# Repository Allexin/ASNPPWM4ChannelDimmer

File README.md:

# ASNPPWM4ChannelDimmer
ASNP pwm dimmer with 4 AC 220v channels

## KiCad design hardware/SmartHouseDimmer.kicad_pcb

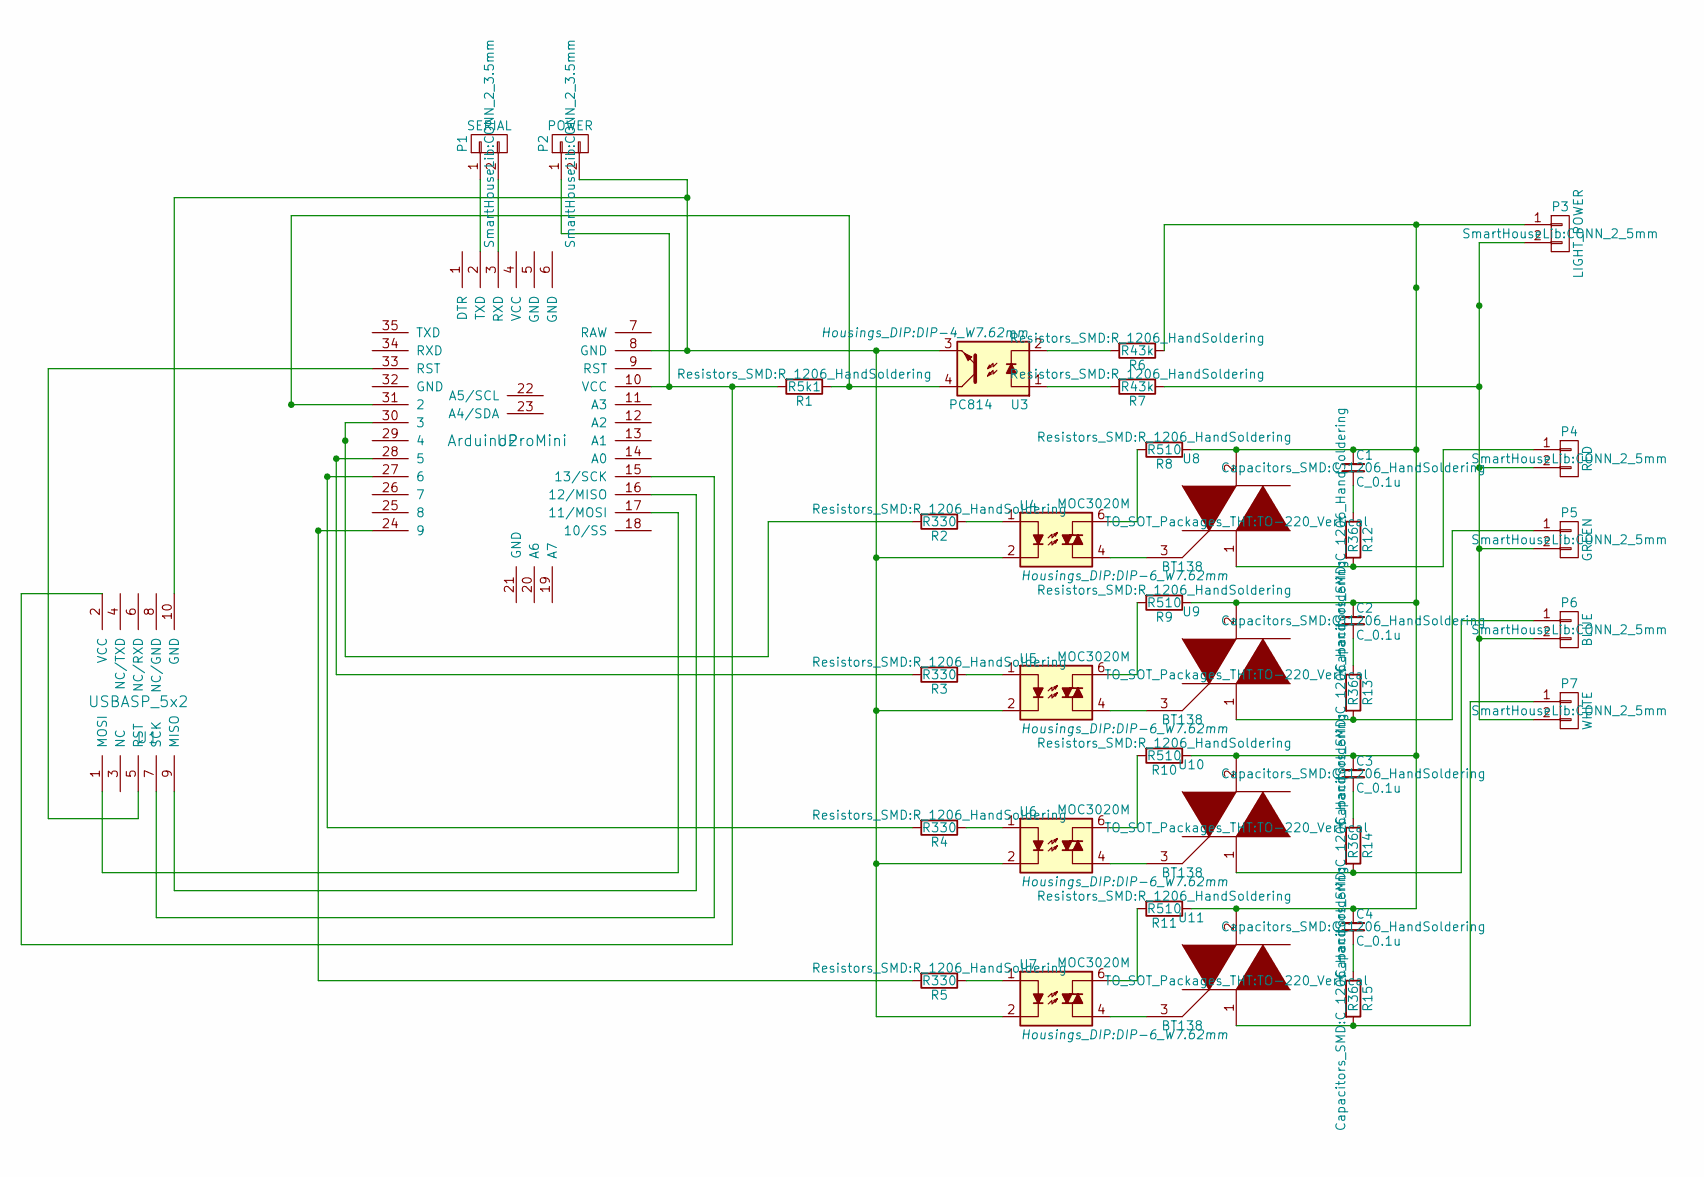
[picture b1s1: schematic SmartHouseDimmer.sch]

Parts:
C1, C2, C3, C4: C_0.1u; C_1206_HandSoldering
P1: SERIAL; CONN_2_3.5mm
P2: POWER; CONN_2_3.5mm
P3: LIGHT_POWER; CONN_2_5mm
P4: RED; CONN_2_5mm
P5: GREEN; CONN_2_5mm
P6: BLUE; CONN_2_5mm
P7: WHITE; CONN_2_5mm
R1: R5k1; R_1206_HandSoldering
R2, R3, R4, R5: R330; R_1206_HandSoldering
R6, R7: R43k; R_1206_HandSoldering
R8, R9, R10, R11: R510; R_1206_HandSoldering
R12, R13, R14, R15: R36; C_1206_HandSoldering
U1: USBASP_5x2; Pin_Header_Straight_2x05_Pitch2.54mm
U2: ArduinoProMini
U3: PC814; DIP-4_W7.62mm
U4, U5, U6, U7: MOC3020M; DIP-6_W7.62mm
U8, U9, U10, U11: BT138; TO-220_Vertical

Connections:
unnamed: C1.1, C2.1, C3.1, C4.1, P3.1, R6.1, R8.1, R9.1, R10.1, R11.1, U8.2, U9.2, U10.2, U11.2
unnamed: C1.2, R12.1
unnamed: C2.2, R13.1
unnamed: C3.2, R14.1
unnamed: C4.2, R15.1
unnamed: P1.1, U2.2 (TXD)
unnamed: P1.2, U2.3 (RXD)
unnamed: P2.1, R1.2, U1.2 (VCC), U2.10 (VCC)
unnamed: P2.2, U1.10 (GND), U2.8 (GND), U3.3, U4.2, U5.2, U6.2, U7.2
unnamed: P3.2, P4.2, P5.2, P6.2, P7.2, R7.1
unnamed: P4.1, R12.2, U8.1
unnamed: P5.1, R13.2, U9.1
unnamed: P6.1, R14.2, U10.1
unnamed: P7.1, R15.2, U11.1
unnamed: R1.1, U2.31 (2), U3.4
unnamed: R2.1, U4.1
unnamed: R2.2, U2.30 (3)
unnamed: R3.1, U5.1
unnamed: R3.2, U2.28 (5)
unnamed: R4.1, U6.1
unnamed: R4.2, U2.27 (6)
unnamed: R5.1, U7.1
unnamed: R5.2, U2.24 (9)
unnamed: R6.2, U3.2
unnamed: R7.2, U3.1
unnamed: R8.2, U4.6
unnamed: R9.2, U5.6
unnamed: R10.2, U6.6
unnamed: R11.2, U7.6
unnamed: U1.1 (MOSI), U2.17 (11/MOSI)
unnamed: U1.5 (RST), U2.33 (RST)
unnamed: U1.7 (SCK), U2.15 (13/SCK)
unnamed: U1.9 (MISO), U2.16 (12/MISO)
unnamed: U4.4, U8.3
unnamed: U5.4, U9.3
unnamed: U6.4, U10.3
unnamed: U7.4, U11.3

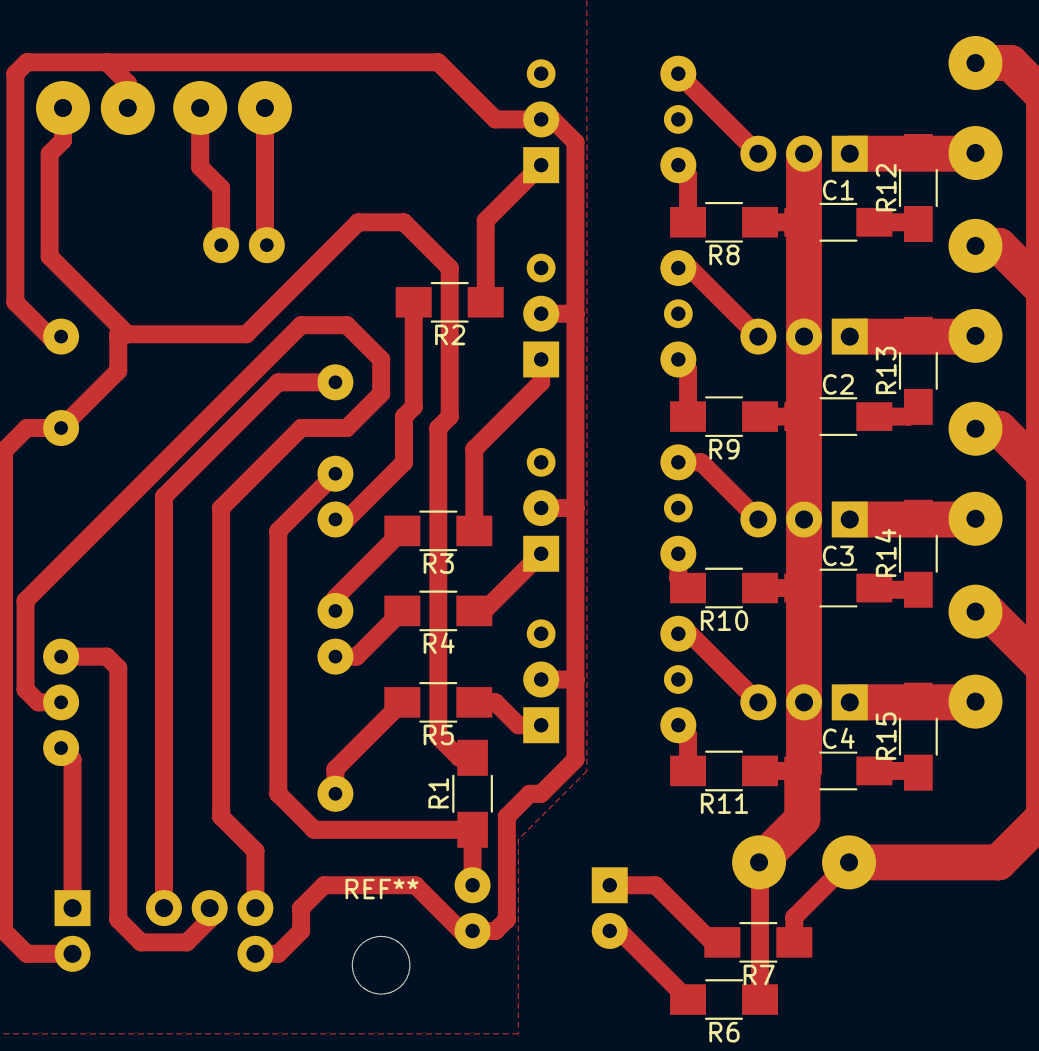
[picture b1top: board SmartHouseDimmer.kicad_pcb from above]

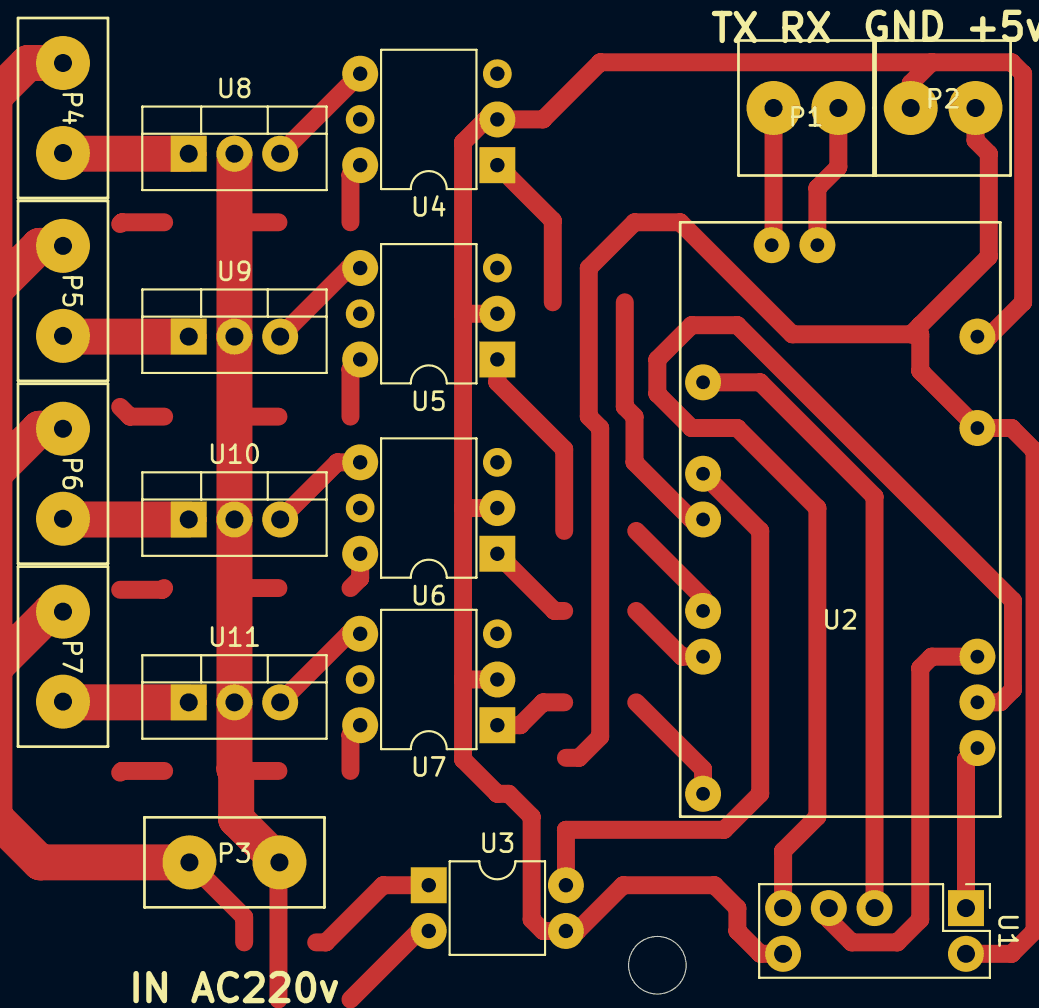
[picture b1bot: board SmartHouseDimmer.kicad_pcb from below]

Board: 2 copper layers, 37 parts (18 on the bottom side), 37 nets.

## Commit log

2017-12-25 -First release
2017-12-25 -PCB
